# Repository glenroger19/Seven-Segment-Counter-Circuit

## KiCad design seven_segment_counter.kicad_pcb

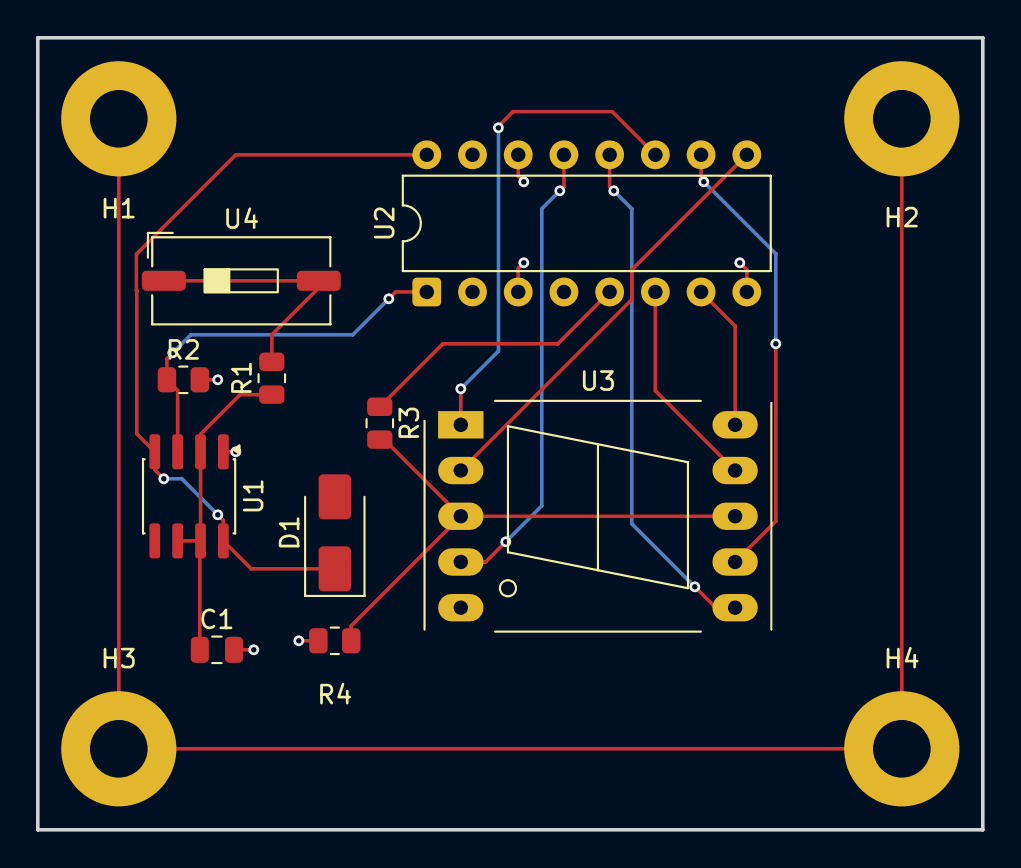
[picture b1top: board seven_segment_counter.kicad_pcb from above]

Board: 2 copper layers, 52.5 x 44.0 mm, 14 parts (0 on the bottom side), 15 nets.

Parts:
C1: 0.01u; C_0805_2012Metric
D1: D; D_SMA
H1, H2, H3, H4: MountingHole_Pad; MountingHole_3.2mm_M3_Pad
R1, R3: 47k; R_0805_2012Metric
R2: 220k; R_0805_2012Metric
R4: 470R; R_0805_2012Metric
U1: NE555D; SOIC-8_3.9x4.9mm_P1.27mm
U2: CD4033B; DIP-16_W7.62mm
U3: SM420561N; 7SegmentLED_LTS6760_LTS6780
U4: SW_DIP_SPSTx01_Slide_9.78x4.72mm_W8.61mm_P2.54mm

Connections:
GND: C1.2, R2.2, R4.1, U1.1 (GND), U2.3 (RIPPLE_BLANKING_IN), U2.8 (V_{SS}), U2.14 (LAMP_TEST)
GNDD: H1.1 (1_1), H2.1 (1_1), H3.1 (1_1), H4.1 (1_1)
unnamed: D1.1 (K), U1.4 (~RST), U1.8 (VCC), U2.16 (V_{DD})
unnamed: R1.2, U4.1 (A), U4.2 (A)
unnamed: R3.2, R4.2, U3.3 (CC), U3.8 (CC)
unnamed: C1.1, R1.1, U1.2 (TRIG), U1.6 (THRES), U1.7 (DISCH)
unnamed: R2.1, U1.3 (OUT), U2.1 (CLOCK)
unnamed: R3.1, U2.5 (CARRY_OUT)
unnamed: U2.10 (a), U3.7 (A)
unnamed: U2.12 (b), U3.6 (B)
unnamed: U2.13 (c), U3.4 (C)
unnamed: U2.9 (d), U3.2 (D)
unnamed: U2.11 (e), U3.1 (E)
unnamed: U2.6 (f), U3.9 (F)
unnamed: U2.7 (g), U3.10 (G)
